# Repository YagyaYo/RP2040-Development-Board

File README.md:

RP2040 Development Board
A custom RP2040 development board designed from the ground up, with the GPIO reference built directly into the PCB.

Why I Built This
I got tired of constantly checking the Raspberry Pi Pico pinout reference while prototyping.

So I decided to design my own RP2040 development board and put the reference information directly onto the silkscreen.

Every GPIO header is labeled with its supported alternate functions, making it easier to identify connections, wire peripherals, and debug without repeatedly opening a datasheet.
Hardware
- MCU: Raspberry Pi RP2040
- Flash: W25Q16JV external QSPI flash
- Clock: 12 MHz crystal
- Power: USB-C with AP2112K-3.3 voltage regulator
- Interfaces: GPIO, UART, SPI, I²C, PWM, ADC
- Debugging: Dedicated SWD header
- Boot: Manual BOOT control
- Design: Custom schematic, PCB layout, routing, and silkscreen
Design Files
File	Description
RP2040.kicad_pcb	KiCad PCB layout
schematic.pdf	Complete circuit schematic
images/	3D PCB renders

**I also included gerber files but it is based for JLCPCB. If that works out fine for you feel free to check out the Bill of Materials and CPL file**

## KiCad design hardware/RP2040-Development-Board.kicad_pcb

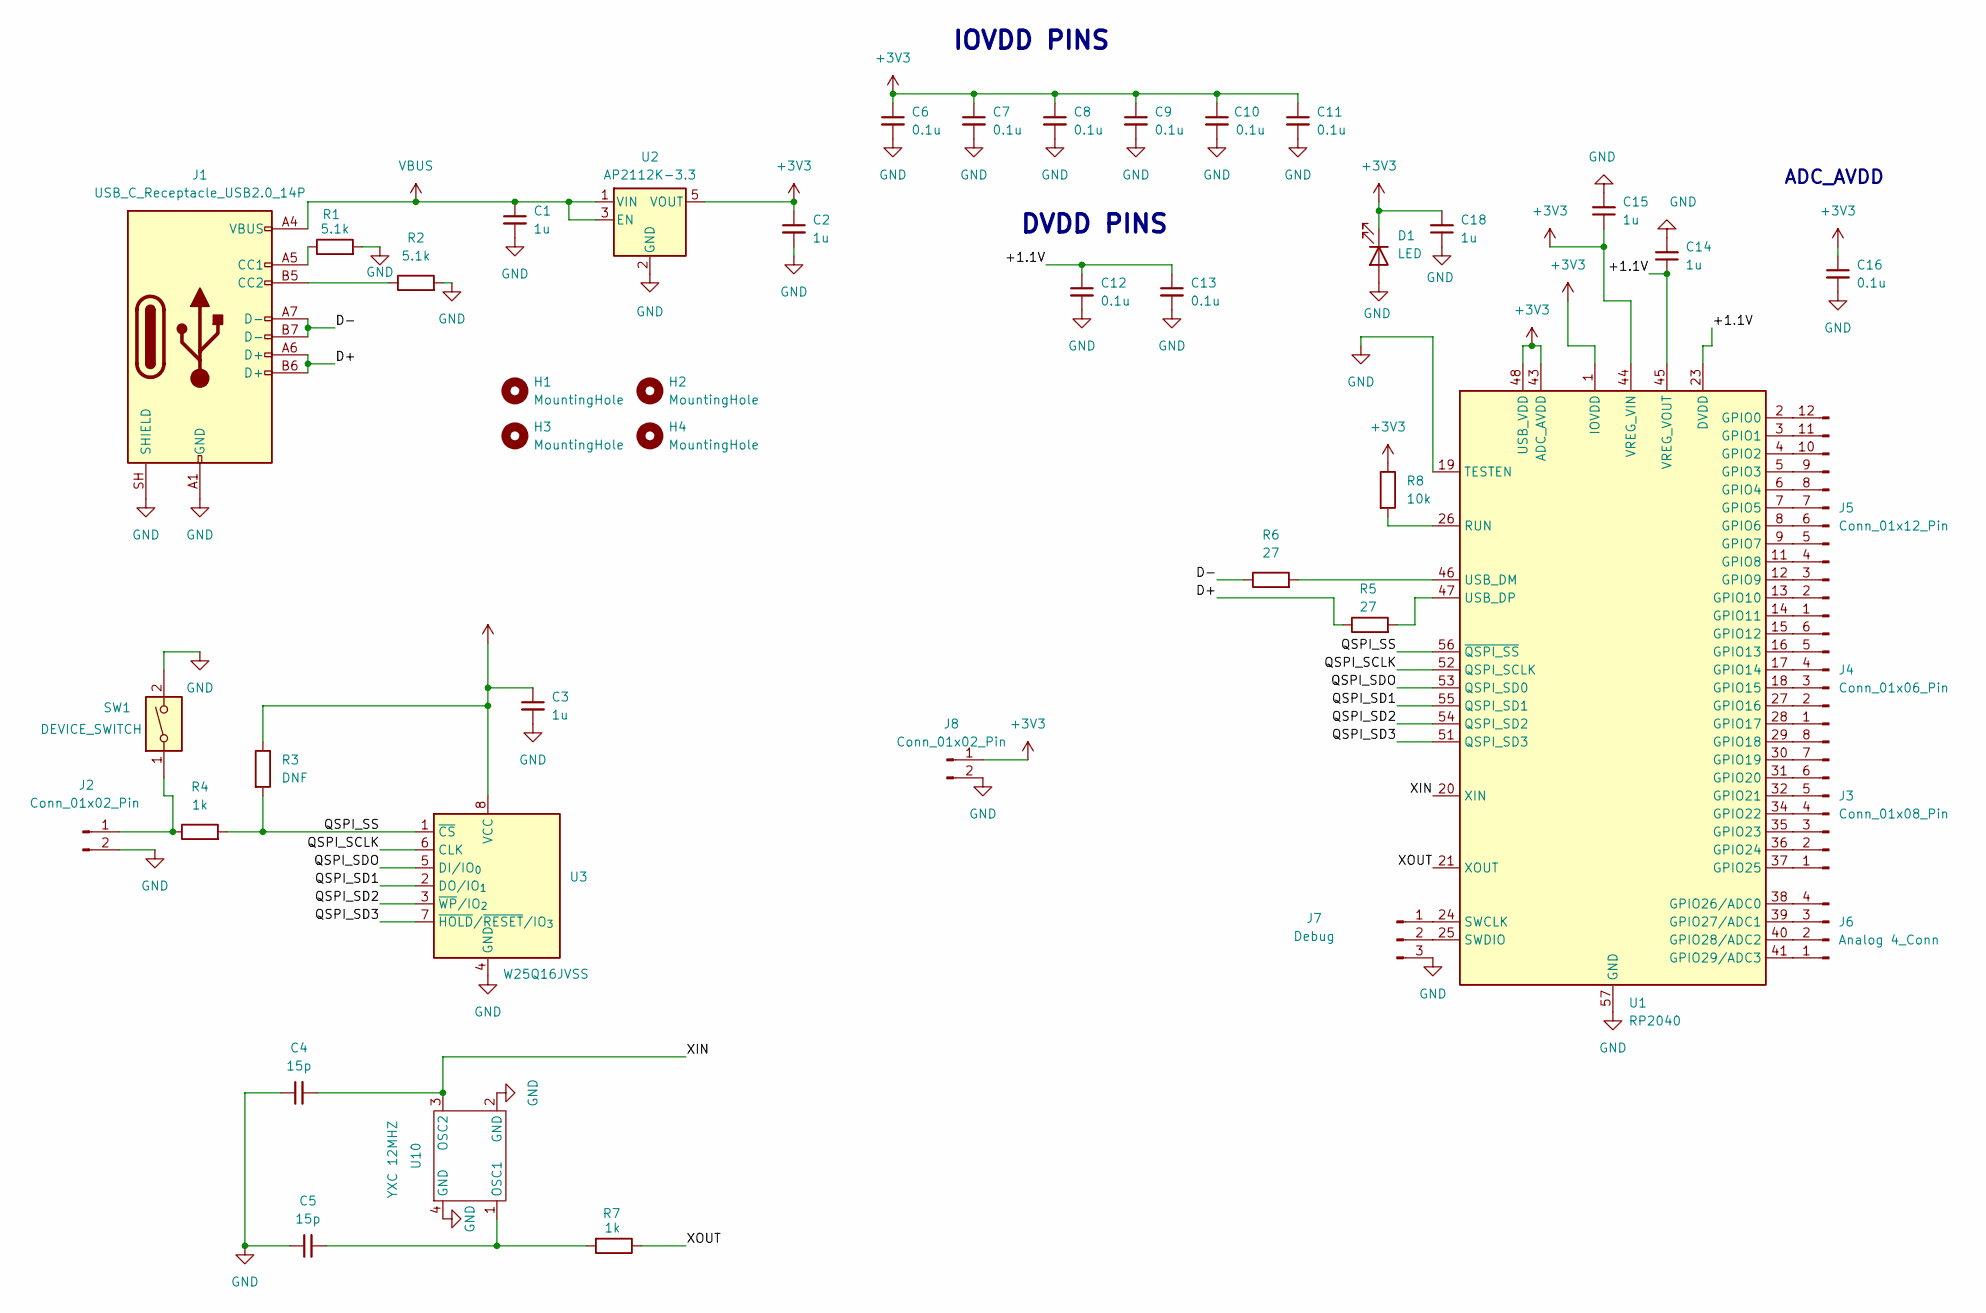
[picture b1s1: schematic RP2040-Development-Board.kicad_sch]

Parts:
C1, C2, C3, C14, C15, C18: 1u; C_0402_1005Metric
C4, C5: 15p; C_0402_1005Metric
C6, C7, C8, C9, C10, C11, C12, C13, C16: 0.1u; C_0402_1005Metric
D1: LED; LED_0603_1608Metric
H1, H2, H3, H4: MountingHole; MountingHole_2.2mm_M2
J1: USB_C_Receptacle_USB2.0_14P; USB_C_Receptacle_HRO_TYPE-C-31-M-12
J2, J8: Conn_01x02_Pin; PinSocket_1x02_P2.54mm_Vertical
J3: Conn_01x08_Pin; PinSocket_1x08_P2.54mm_Vertical
J4: Conn_01x06_Pin; PinSocket_1x06_P2.54mm_Vertical
J5: Conn_01x12_Pin; PinSocket_1x12_P2.54mm_Vertical
J6: Analog 4_Conn; PinSocket_1x04_P2.54mm_Vertical
J7: Debug; PinHeader_1x03_P2.54mm_Vertical
R1, R2: 5.1k; R_0603_1608Metric
R3: DNF; R_0603_1608Metric
R4, R7: 1k; R_0603_1608Metric
R5, R6: 27; R_0603_1608Metric
R8: 10k; R_0603_1608Metric
SW1: DEVICE_SWITCH; SW_DIP_SPSTx01_Slide_6.7x4.1mm_W6.73mm_P2.54mm_LowProfile_J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
U1: RP2040; QFN-56-1EP_7x7mm_P0.4mm_EP3.2x3.2mm
U2: AP2112K-3.3; SOT-23-5_HandSoldering
U3: W25Q16JVSS; SOIC-8_5.3x5.3mm_P1.27mm
U10: YXC 12MHZ; Crystal_SMD_3225-4Pin_3.2x2.5mm_HandSoldering

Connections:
+3V3: C2.1, C3.1, C6.1, C7.1, C8.1, C9.1, C10.1, C11.1, C15.1, C16.1, C18.2, D1.1 (K), J8.1, R3.1, R8.1, U1.1 (IOVDD), U1.10 (IOVDD), U1.22 (IOVDD), U1.33 (IOVDD), U1.42 (IOVDD), U1.43 (ADC_AVDD), U1.44 (VREG_VIN), U1.48 (USB_VDD), U1.49 (IOVDD), U2.5 (VOUT), U3.8 (VCC); also elsewhere on the board
/+1.1V: C12.1, C13.1, C14.1, U1.23 (DVDD), U1.45 (VREG_VOUT), U1.50 (DVDD)
/D+: J1.A6 (D+), J1.B6 (D+), R5.1
/D-: J1.A7 (D-), J1.B7 (D-), R6.1
/QSPI_SCLK: U1.52 (QSPI_SCLK), U3.6 (CLK)
/QSPI_SD1: U1.55 (QSPI_SD1), U3.2 (DO/IO_{1})
/QSPI_SD2: U1.54 (QSPI_SD2), U3.3 (~WP/IO_{2})
/QSPI_SD3: U1.51 (QSPI_SD3), U3.7 (~HOLD/~RESET/IO_{3})
/QSPI_SDO: U1.53 (QSPI_SD0), U3.5 (DI/IO_{0})
/QSPI_SS: R3.2, R4.2, U1.56 (~QSPI_SS), U3.1 (~CS)
/XIN: C4.2, U1.20 (XIN), U10.3 (OSC2)
/XOUT: R7.1, U1.21 (XOUT)
GND: C1.2, C2.2, C3.2, C4.1, C5.1, C6.2, C7.2, C8.2, C9.2, C10.2, C11.2, C12.2, C13.2, C14.2, C15.2, C16.2, C18.1, D1.2 (A), J1.A1 (GND), J1.A12 (GND), J1.B1 (GND), J1.B12 (GND), J1.SH (SHIELD), J2.2, J7.3, J8.2, R1.2, R2.2, SW1.2, U1.19 (TESTEN), U1.57 (GND), U2.2 (GND), U3.4 (GND), U10.2 (GND), U10.4 (GND)
unnamed: J1.A5 (CC1), R1.1
unnamed: J1.B5 (CC2), R2.1
unnamed: J2.1, R4.1, SW1.1
unnamed: J3.1, U1.37 (GPIO25)
unnamed: J3.2, U1.36 (GPIO24)
unnamed: J3.3, U1.35 (GPIO23)
unnamed: J3.4, U1.34 (GPIO22)
unnamed: J3.5, U1.32 (GPIO21)
unnamed: J3.6, U1.31 (GPIO20)
unnamed: J3.7, U1.30 (GPIO19)
unnamed: J3.8, U1.29 (GPIO18)
unnamed: J4.1, U1.28 (GPIO17)
unnamed: J4.2, U1.27 (GPIO16)
unnamed: J4.3, U1.18 (GPIO15)
unnamed: J4.4, U1.17 (GPIO14)
unnamed: J4.5, U1.16 (GPIO13)
unnamed: J4.6, U1.15 (GPIO12)
unnamed: J5.1, U1.14 (GPIO11)
unnamed: J5.2, U1.13 (GPIO10)
unnamed: J5.3, U1.12 (GPIO9)
unnamed: J5.4, U1.11 (GPIO8)
unnamed: J5.5, U1.9 (GPIO7)
unnamed: J5.6, U1.8 (GPIO6)
unnamed: J5.7, U1.7 (GPIO5)
unnamed: J5.8, U1.6 (GPIO4)
unnamed: J5.9, U1.5 (GPIO3)
unnamed: J5.10, U1.4 (GPIO2)
unnamed: J5.11, U1.3 (GPIO1)
unnamed: J5.12, U1.2 (GPIO0)
unnamed: J6.1, U1.41 (GPIO29/ADC3)
unnamed: J6.2, U1.40 (GPIO28/ADC2)
unnamed: J6.3, U1.39 (GPIO27/ADC1)
unnamed: J6.4, U1.38 (GPIO26/ADC0)
unnamed: J7.1, U1.24 (SWCLK)
unnamed: J7.2, U1.25 (SWDIO)
unnamed: R8.2, U1.26 (RUN)
unnamed: R6.2, U1.46 (USB_DM)
unnamed: R5.2, U1.47 (USB_DP)
unnamed: C5.2, R7.2, U10.1 (OSC1)
VBUS: C1.1, J1.A4 (VBUS), J1.A9 (VBUS), J1.B4 (VBUS), J1.B9 (VBUS), U2.1 (VIN), U2.3 (EN)

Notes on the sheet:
IOVDD PINS
DVDD PINS
ADC_AVDD

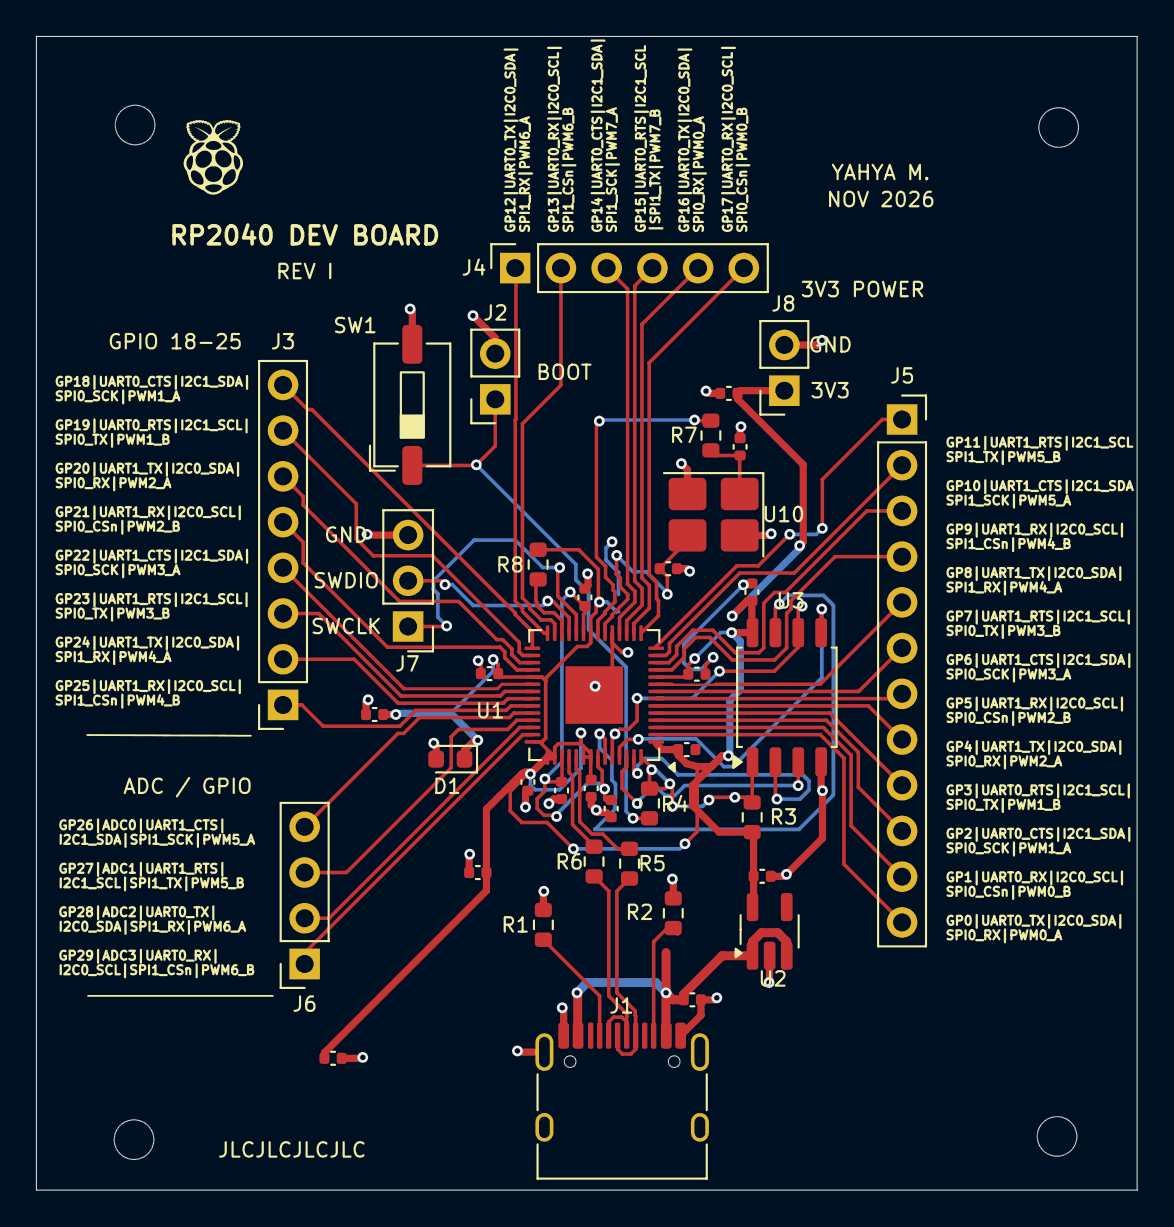
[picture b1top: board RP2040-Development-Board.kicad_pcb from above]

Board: 2 copper layers, 61.2 x 64.1 mm, 44 parts (1 on the bottom side), 53 nets.

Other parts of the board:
C17: 0.1u; C_0402_1005Metric

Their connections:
+3V3: C17.1; also elsewhere on the board

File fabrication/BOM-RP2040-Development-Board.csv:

Comment,Designator,Footprint,LCSC,Quantity
0.1u,"C10,C11,C12,C13,C16,C17,C6,C7,C8,C9",C_0402_1005Metric,C1525,10
10k,R8,R_0603_1608Metric,C25804,1
15p,"C4,C5",C_0402_1005Metric,C1548,2
1k,R7,R_0603_1608Metric,C20197,1
1k,R4,R_0603_1608Metric,C21190,1
1u,"C14,C15",C_0402_1005Metric,C1525,2
1u,"C1,C18,C2,C3",C_0402_1005Metric,C52923,4
27,"R5,R6",R_0603_1608Metric,C25190,2
5.1k,"R1,R2",R_0603_1608Metric,C23186,2
AP2112K-3.3,U2,SOT-23-5_HandSoldering,C51118,1
LED,D1,LED_0603_1608Metric,C2286,1
RP2040,U1,QFN-56-1EP_7x7mm_P0.4mm_EP3.2x3.2mm,C2040,1
USB_C_Receptacle_USB2.0_14P,J1,USB_C_Receptacle_HRO_TYPE-C-31-M-12,C3151746,1
W25Q16JVSS,U3,SOIC-8_5.3x5.3mm_P1.27mm,C131025,1
YXC 12MHZ,U10,Crystal_SMD_3225-4Pin_3.2x2.5mm_HandSoldering,C9002,1
Conn_01x12_Pin,J5,PinSocket_1x12_P2.54mm_Vertical,,1
Analog 4_Conn,J6,PinSocket_1x04_P2.54mm_Vertical,,1
DEVICE_SWITCH,SW1,SW_DIP_SPSTx01_Slide_6.7x4.1mm_W6.73mm_P2.54mm_LowProfile_JPin,,1
Conn_01x02_Pin,J2,PinSocket_1x02_P2.54mm_Vertical,,1
Conn_01x08_Pin,J3,PinSocket_1x08_P2.54mm_Vertical,,1
Conn_01x06_Pin,J4,PinSocket_1x06_P2.54mm_Vertical,,1
DNF,R3,R_0603_1608Metric,,1
Conn_01x02_Pin,J8,PinSocket_1x02_P2.54mm_Vertical,,1
Debug,J7,PinHeader_1x03_P2.54mm_Vertical,,1
